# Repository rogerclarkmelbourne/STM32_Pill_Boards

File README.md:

# STM32_Pill_Boards

This repo contains a KiCad conversion of the STM32STAMP board and also two new BluePill F4 boards designed by @racemaniac and @Squonk42

My previous attemps have been deleted.

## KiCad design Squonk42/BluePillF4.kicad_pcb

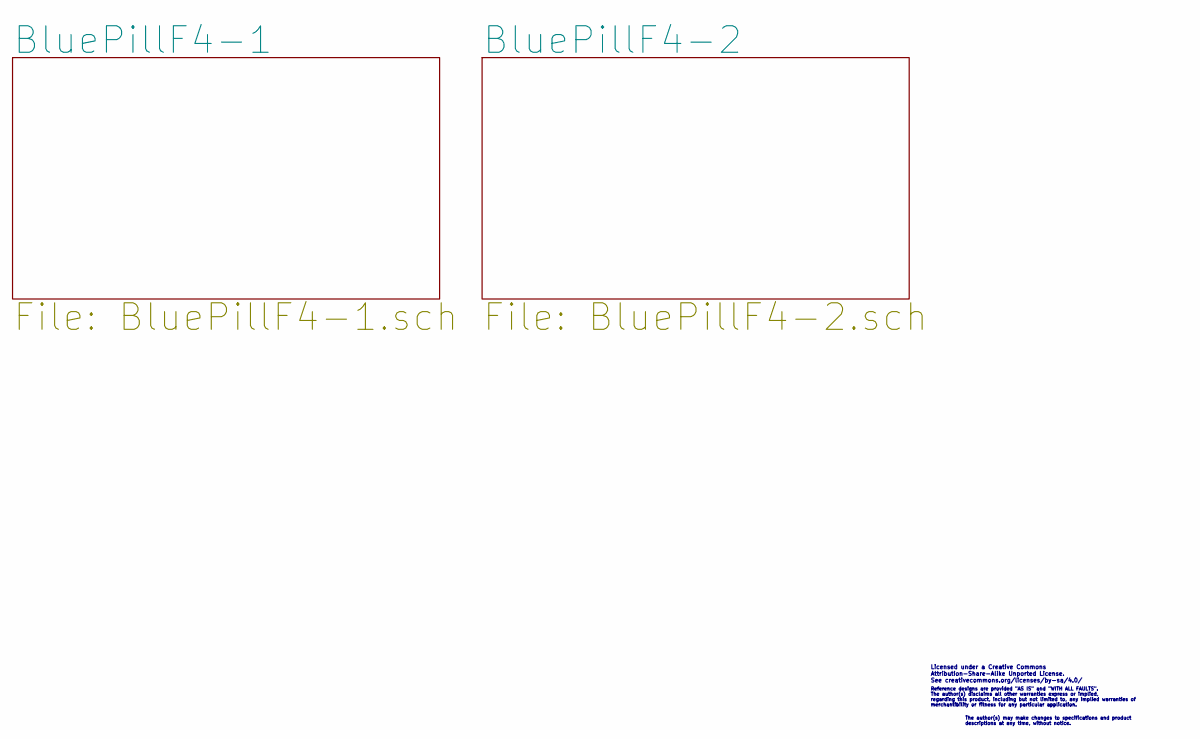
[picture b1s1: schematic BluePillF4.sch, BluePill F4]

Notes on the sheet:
Licensed under a Creative Commons Attribution-Share-Alike Unported License. See creativecommons.org/licenses/by-sa/4.0/
Reference designs are provided "AS IS" and "WITH ALL FAULTS".
The author(s) disclaims all other warranties express or implied,
regarding this product, including but not limited to, any implied warranties of
merchantibility or fitness for any particular application.
The author(s) may make changes to specifications and product
descriptions at any time, without notice.

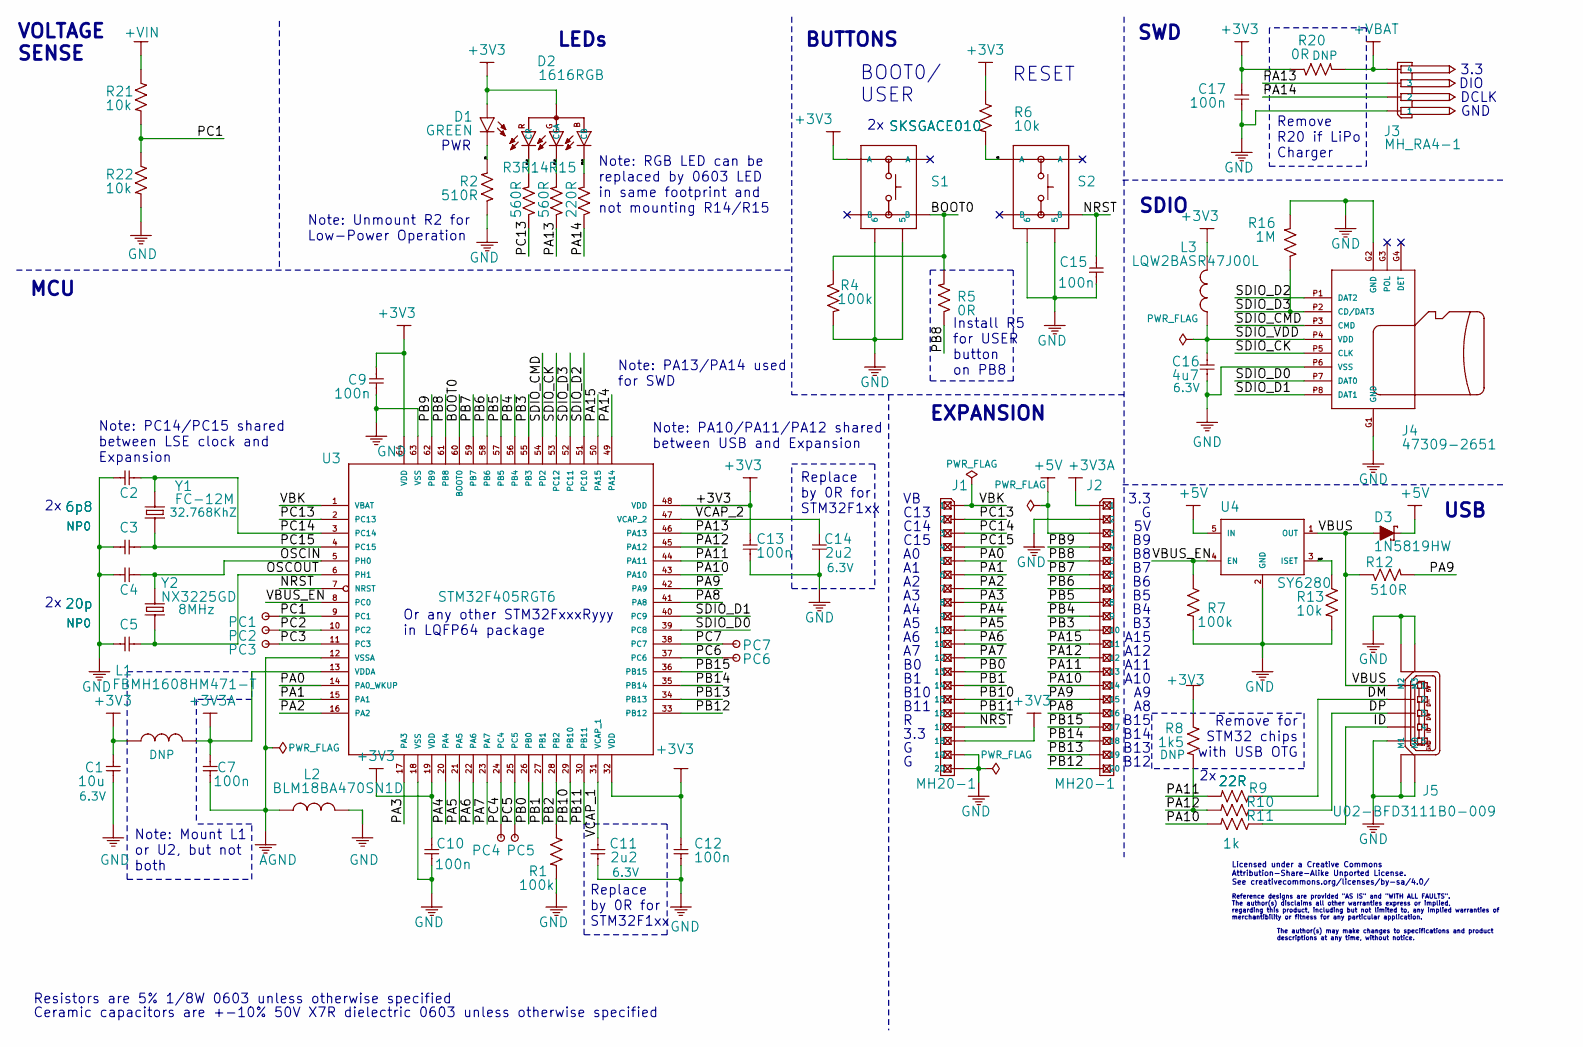
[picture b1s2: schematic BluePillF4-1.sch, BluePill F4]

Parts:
C1: 10u; C0603; PARTNO C0603_10u_X7R_10%_CER_6V3
C2, C3: 6p8; C0603; PARTNO C0603_6p8_NP0_5%_CER_50V
C4, C5: 20p; C0603; PARTNO C0603_20p_NP0_5%_CER_50V
C7, C9, C10, C12, C13, C15, C17: 100n; C0603; PARTNO C0603_100n_X7R_10%_CER_50V
C11, C14: 2u2; C0603; PARTNO C0603_2u2_X7R_10%_CER_6V3
C16: 4u7; C0603; PARTNO C0603_4u7_X7R_10%_CER_6V3
D1: GREEN; LED0603; PARTNO LED0603-GREEN
D2: 1616RGB; PARTNO LED1616-RGB
D3: 1N5819HW; SOD-123; PARTNO 1N5819HW
J1, J2: MH20-1; MH20-1-0.1; PARTNO MH20-1-0.1
J3: MH_RA4-1; MH_RA4-1-0.1; PARTNO MH_RA4-1-0.1
J4: 47309-2651; PARTNO 47309-2651
J5: U02-BFD3111B0-009; PARTNO U02-BFD3111B0-009
L1: FBMH1608HM471-T; FB0603; PARTNO FBMH1608HM471-T
L2: BLM18BA470SN1D; FB0603; PARTNO BLM18BA470SN1D
L3: LQW2BASR47J00L; FB0805; PARTNO LQW2BASR47J00L
PC1, PC2, PC3, PC4, PC5, PC6, PC7: TEST_PAD
R1, R4, R7: 100k; R0603; PARTNO R0603_100k_5%_125mW
R2, R12: 510R; R0603; PARTNO R0603_510R_5%_125mW
R3, R14: 560R; R0603; PARTNO R0603_510R_5%_125mW
R5, R20: 0R; R0603; PARTNO R0603_510R_5%_125mW
R6, R13, R21, R22: 10k; R0603; PARTNO R0603_10k_5%_125mW
R8: 1k5; R0603; PARTNO R0603_1k5_5%_125mW
R9, R10: 22R; R0603; PARTNO R0603_22R_5%_125mW
R11: 1k; R0603; PARTNO R0603_1k_5%_125mW
R15: 220R; R0603; PARTNO R0603_510R_5%_125mW
R16: 1M; R0603; PARTNO R0603_1M_5%_125mW
S1, S2: SKSGACE010; PARTNO SKSGACE010
U3: STM32F405RGT6; LQFP64; PARTNO STM32F405RGT6
U4: SY6280; SOT23-5; PARTNO SY6280AAC
Y1: FC-12M; PARTNO FC-12M 32.7680KA-A3
Y2: NX3225GD; CRYSTAL_32X25_2P; PARTNO NX3225GD-8MHZ-STD-CRA-3

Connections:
+3V3: C1.1, C9.2, C10.2, C12.1, C13.1, C17.2, D1.2 (A), D2.4 (A), J1.18, L1.1, L3.2, R6.1, R8.1, R20.1, S1.3 (A), U3.19 (VDD), U3.32 (VDD), U3.48 (VDD), U3.64 (VDD); also elsewhere on the board
+3V3A: C7.2, J2.1, L1.2, U3.13 (VDDA); also elsewhere on the board
+5V: D3.C, J2.3, U4.5 (IN); also elsewhere on the board
+VBAT: J3.4, R20.2; also elsewhere on the board
+VIN: R21.1; also elsewhere on the board
/BluePillF4-1/BOOT0: R4.1, R5.2, S1.2 (B), U3.60 (BOOT0)
/BluePillF4-1/D1: D1.1 (C), R2.2
/BluePillF4-1/D2_B: D2.3 (CB), R15.2
/BluePillF4-1/D2_G: D2.2 (CG), R14.2
/BluePillF4-1/D2_R: D2.1 (CR), R3.2
/BluePillF4-1/DM: J5.2, R9.1
/BluePillF4-1/DP: J5.3, R10.1
/BluePillF4-1/ID: J5.4, R11.1
/BluePillF4-1/ISET: R13.1, U4.3 (ISET)
/BluePillF4-1/NRST: C15.2, J1.17, S2.2 (B), U3.7 (NRST)
/BluePillF4-1/OSCIN: C4.1, U3.5 (PH0), Y2.2
/BluePillF4-1/OSCOUT: C5.1, U3.6 (PH1), Y2.1
/BluePillF4-1/PA0: J1.5, U3.14 (PA0_WKUP)
/BluePillF4-1/PA1: J1.6, U3.15 (PA1)
/BluePillF4-1/PA2: J1.7, U3.16 (PA2)
/BluePillF4-1/PA3: J1.8, U3.17 (PA3)
/BluePillF4-1/PA4: J1.9, U3.20 (PA4)
/BluePillF4-1/PA5: J1.10, U3.21 (PA5)
/BluePillF4-1/PA6: J1.11, U3.22 (PA6)
/BluePillF4-1/PA7: J1.12, U3.23 (PA7)
/BluePillF4-1/PA8: J2.16, U3.41 (PA8)
/BluePillF4-1/PA9: J2.15, R12.2, U3.42 (PA9)
/BluePillF4-1/PA10: J2.14, R11.2, U3.43 (PA10)
/BluePillF4-1/PA11: J2.13, R9.2, U3.44 (PA11)
/BluePillF4-1/PA12: J2.12, R8.2, R10.2, U3.45 (PA12)
/BluePillF4-1/PA13: J3.3, R14.1, U3.46 (PA13)
/BluePillF4-1/PA14: J3.2, R15.1, U3.49 (PA14)
/BluePillF4-1/PA15: J2.11, U3.50 (PA15)
/BluePillF4-1/PB0: J1.13, U3.26 (PB0)
/BluePillF4-1/PB1: J1.14, U3.27 (PB1)
/BluePillF4-1/PB2: R1.1, U3.28 (PB2)
/BluePillF4-1/PB3: J2.10, U3.55 (PB3)
/BluePillF4-1/PB4: J2.9, U3.56 (PB4)
/BluePillF4-1/PB5: J2.8, U3.57 (PB5)
/BluePillF4-1/PB6: J2.7, U3.58 (PB6)
/BluePillF4-1/PB7: J2.6, U3.59 (PB7)
/BluePillF4-1/PB8: J2.5, R5.1, U3.61 (PB8)
/BluePillF4-1/PB9: J2.4, U3.62 (PB9)
/BluePillF4-1/PB10: J1.15, U3.29 (PB10)
/BluePillF4-1/PB11: J1.16, U3.30 (PB11)
/BluePillF4-1/PB12: J2.20, U3.33 (PB12)
/BluePillF4-1/PB13: J2.19, U3.34 (PB13)
/BluePillF4-1/PB14: J2.18, U3.35 (PB14)
/BluePillF4-1/PB15: J2.17, U3.36 (PB15)
/BluePillF4-1/PC1: PC1.1, R21.2, R22.1, U3.9 (PC1)
/BluePillF4-1/PC2: PC2.1, U3.10 (PC2)
/BluePillF4-1/PC3: PC3.1, U3.11 (PC3)
/BluePillF4-1/PC4: PC4.1, U3.24 (PC4)
/BluePillF4-1/PC5: PC5.1, U3.25 (PC5)
/BluePillF4-1/PC6: PC6.1, U3.37 (PC6)
/BluePillF4-1/PC7: PC7.1, U3.38 (PC7)
/BluePillF4-1/PC13: J1.2, R3.1, U3.2 (PC13)
/BluePillF4-1/PC14: C2.1, J1.3, U3.3 (PC14), Y1.1
/BluePillF4-1/PC15: C3.1, J1.4, U3.4 (PC15), Y1.2
/BluePillF4-1/R6: R6.2, S2.3 (A)
/BluePillF4-1/SDIO_CK: J4.P5 (CLK), U3.53 (PC12)
/BluePillF4-1/SDIO_CMD: J4.P3 (CMD), U3.54 (PD2)
/BluePillF4-1/SDIO_D0: J4.P7 (DAT0), U3.39 (PC8)
/BluePillF4-1/SDIO_D1: J4.P8 (DAT1), U3.40 (PC9)
/BluePillF4-1/SDIO_D2: J4.P1 (DAT2), U3.51 (PC10)
/BluePillF4-1/SDIO_D3: J4.P2 (CD/DAT3), R16.1, U3.52 (PC11)
/BluePillF4-1/SDIO_VDD: C16.2, J4.P4 (VDD), L3.1
/BluePillF4-1/VBK: J1.1, U3.1 (VBAT)
/BluePillF4-1/VBUS: D3.A, J5.1, R12.1, U4.1 (OUT)
/BluePillF4-1/VBUS_EN: R7.1, U3.8 (PC0), U4.4 (EN)
/BluePillF4-1/VCAP_1: C11.2, U3.31 (VCAP_1)
/BluePillF4-1/VCAP_2: C14.2, U3.47 (VCAP_2)
AGND: C7.1, L2.1, U3.12 (VSSA); also elsewhere on the board
GND: C1.2, C2.2, C3.2, C4.2, C5.2, C9.1, C10.1, C11.1, C12.2, C13.2, C14.1, C15.1, C16.1, C17.1, J1.19, J1.20, J2.2, J3.1, J4.G1 (GND), J4.G2 (GND), J4.P6 (VSS), J5.5, J5.S$1 (M0), J5.S$2 (M1), J5.S$3 (M2), J5.S$4 (M3), L2.2, R1.2, R2.1, R4.2, R7.2, R13.2, R16.2, R22.2, S1.5, S1.6, S2.5, S2.6, U3.18 (VSS), U3.63 (VSS), U4.2 (GND); also elsewhere on the board

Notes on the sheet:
Reference designs are provided "AS IS" and "WITH ALL FAULTS".
regarding this product, including but not limited to, any implied warranties of
The author(s) may make changes to specifications and product
The author(s) disclaims all other warranties express or implied,
merchantibility or fitness for any particular application.
descriptions at any time, without notice.
Ceramic capacitors are +-10% 50V X7R dielectric 0603 unless otherwise specified
Resistors are 5% 1/8W 0603 unless otherwise specified
Remove for STM32 chips with USB OTG
Replace by 0R for STM32F1xx
RESET
BOOT0/ USER
SWD
USB
LEDs
Install R5 for USER button on PB8
PWR
SDIO
BUTTONS
EXPANSION
MCU
Note: PC14/PC15 shared between LSE clock and Expansion
Note: PA10/PA11/PA12 shared between USB and Expansion
Note: PA13/PA14 used for SWD
DIO
DCLK
3.3
GND
C13
C14
C15
B10
B11
A15
A12
A11
A10
B15
B14
B13

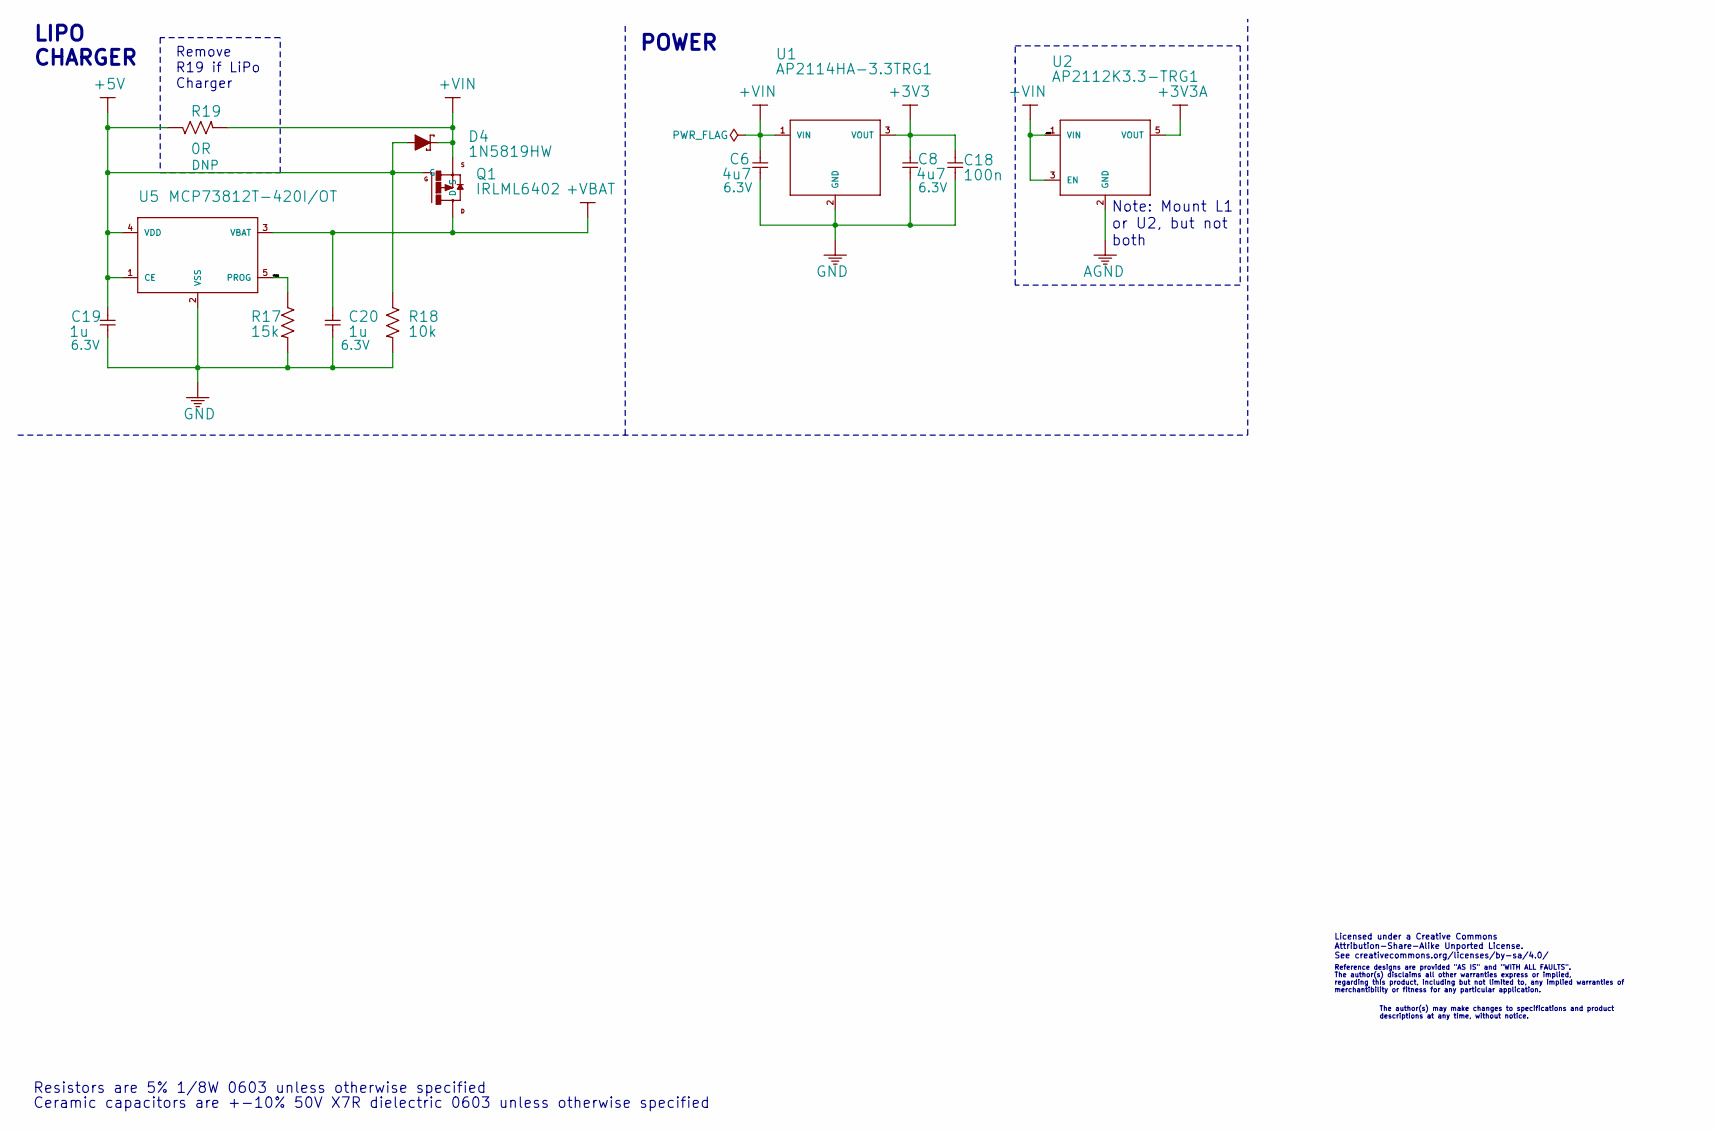
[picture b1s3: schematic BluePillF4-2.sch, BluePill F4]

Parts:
C6, C8: 4u7; C0603; PARTNO C0603_4u7_X7R_10%_CER_6V3
C18: 100n; C0603; PARTNO C0603_100n_X7R_10%_CER_50V
C19, C20: 1u; C0603; PARTNO C0603_1u_X7R_10%_CER_6V3
D4: 1N5819HW; SOD-123; PARTNO 1N5819HW
Q1: IRLML6402; SOT323
R17: 15k; R0603; PARTNO R0603_15k_5%_125mW
R18: 10k; R0603; PARTNO R0603_10k_5%_125mW
R19: 0R; R0603; PARTNO R0603_510R_5%_125mW
U1: AP2114HA-3.3TRG1; SOT223; PARTNO AP2114HA3.3-TRG1
U2: AP2112K3.3-TRG1; SOT23-5; PARTNO AP2112K3.3-TRG1
U5: MCP73812T-420I/OT; SOT23-5

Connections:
+3V3: C8.1, C18.2, U1.3 (VOUT); also elsewhere on the board
+3V3A: U2.5 (VOUT); also elsewhere on the board
+5V: C19.1, D4.A, Q1.1 (G), R18.1, R19.1, U5.1 (CE), U5.4 (VDD); also elsewhere on the board
+VBAT: C20.1, Q1.3 (D), U5.3 (VBAT); also elsewhere on the board
+VIN: C6.1, D4.C, Q1.2 (S), R19.2, U1.1 (VIN), U2.1 (VIN), U2.3 (EN); also elsewhere on the board
/BluePillF4-2/PROG: R17.1, U5.5 (PROG)
AGND: U2.2 (GND); also elsewhere on the board
GND: C6.2, C8.2, C18.1, C19.2, C20.2, R17.2, R18.2, U1.2 (GND), U1.PAD (GND), U5.2 (VSS); also elsewhere on the board

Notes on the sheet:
Licensed under a Creative Commons Attribution-Share-Alike Unported License. See creativecommons.org/licenses/by-sa/4.0/
Reference designs are provided "AS IS" and "WITH ALL FAULTS".
The author(s) disclaims all other warranties express or implied,
regarding this product, including but not limited to, any implied warranties of
merchantibility or fitness for any particular application.
The author(s) may make changes to specifications and product
descriptions at any time, without notice.
LIPO CHARGER
Resistors are 5% 1/8W 0603 unless otherwise specified
Ceramic capacitors are +-10% 50V X7R dielectric 0603 unless otherwise specified
Remove R19 if LiPo Charger
POWER
Note: Mount L1 or U2, but not both

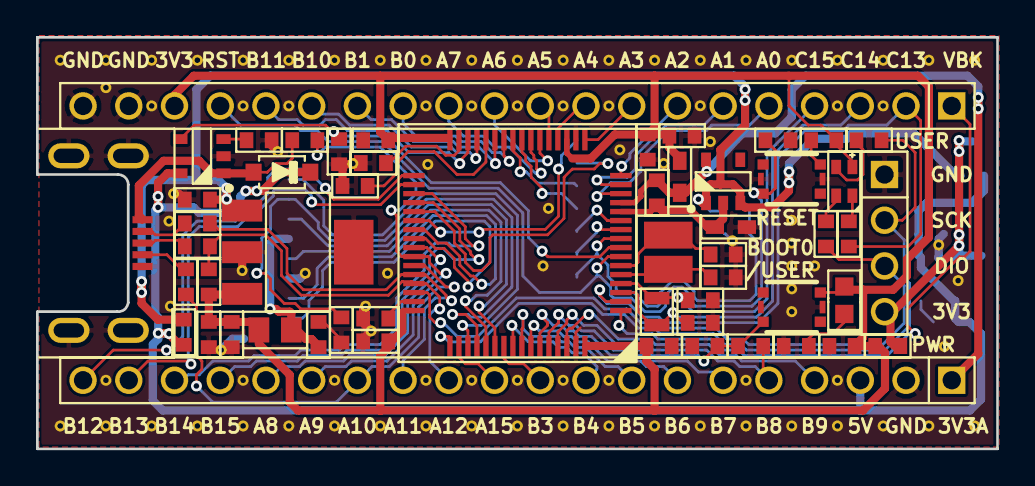
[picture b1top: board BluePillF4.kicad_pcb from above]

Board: 2 copper layers, 53.3 x 22.9 mm, 74 parts (0 on the bottom side), 75 nets.

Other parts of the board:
PC0: TEST_PAD
U$4: OPEN_HARDWARE_LOGO
U$6: RECYCLE_BIN_LOGO

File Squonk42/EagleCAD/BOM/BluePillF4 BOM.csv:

Qty-1,Part References,Value,Package,Part Num,Description,Datasheet,Digi-Key,Mouser,Aliexpress,TaoBao,XREF
1,"R5, R20(DNP)",0R,R0603,***PART# 'R0603_510R_5%_125MW' NOT FOUND***,*,*,*,*,*,*,*
0,"R19(DNP)",0R,R0603,***PART# 'R06030R_5%_125MW' NOT FOUND***,*,*,*,*,*,*,*
1,"R16",1M,R0603,***PART# 'R0603_1M_5%_125MW' NOT FOUND***,*,*,*,*,*,*,*
2,"D3, D4",1N5819HW,SOD-123,***PART# '1N5819HW' NOT FOUND***,*,*,*,*,*,*,*
1,"R11",1k,R0603,***PART# 'R0603_1K_5%_125MW' NOT FOUND***,*,*,*,*,*,*,*
0,"R8(DNP)",1k5,R0603,***PART# 'R0603_1K5_5%_125MW' NOT FOUND***,*,*,*,*,*,*,*
2,"C19, C20",1u,C0603,***PART# 'C0603_1U_X7R_10%_CER_6V3' NOT FOUND***,*,*,*,*,*,*,*
2,"C11, C14",2u2,C0603,***PART# 'C0603_2U2_X7R_10%_CER_6V3' NOT FOUND***,*,*,*,*,*,*,*
3,"C6, C8, C16",4u7,C0603,***PART# 'C0603_4U7_X7R_10%_CER_6V3' NOT FOUND***,*,*,*,*,*,*,*
2,"C2, C3",6p8,C0603,C0603_6P8_NP0_5%_CER_50V,REF9,*,*,*,*,*,*
2,"R21, R22",10k,R0603,***PART# 'R0603_10K_0.1%_125MW' NOT FOUND***,*,*,*,*,*,*,*
2,"R6, R13",10k,R0603,***PART# 'R0603_10K_5%_125MW' NOT FOUND***,*,*,*,*,*,*,*
1,"R18",10k,R0603,***PART# 'R0603_15K_5%_125MW' NOT FOUND***,*,*,*,*,*,*,*
1,"C1",10u,C0603,***PART# 'C0603_10U_X7R_10%_CER_6V3' NOT FOUND***,*,*,*,*,*,*,*
1,"R17",15k,R0603,***PART# 'R0603_15K_5%_125MW' NOT FOUND***,*,*,*,*,*,*,*
2,"C4, C5",20p,C0603,C0603_20P_NP0_5%_CER_50V,REF6,*,*,*,*,*,*
2,"R9, R10",22R,R0603,***PART# 'R0603_22R_5%_125MW' NOT FOUND***,*,*,*,*,*,*,*
3,"R1, R4, R7",100k,R0603,***PART# 'R0603_100K_5%_125MW' NOT FOUND***,*,*,*,*,*,*,*
8,"C7, C9, C10, C12, C13, C15, C17, C18",100n,C0603,C0603_100N_X7R_10%_CER_50V,REF4,*,*,*,*,*,*
5,"R15, R2, R12, R3, R14",560R,R0603,***PART# 'R0603_510R_5%_125MW' NOT FOUND***,*,*,*,*,*,*,*
1,"D2",1616RGB,1616RGB,***PART# 'LED1616-RGB' NOT FOUND***,*,*,*,*,*,*,*
1,"J4",47309-2851,47309-2851,***PART# '47309-2851' NOT FOUND***,*,*,*,*,*,*,*
0,"U2(DNP)",AP2112K3.3-TRG1,SOT23-5,***PART# 'AP2112K3.3-TRG1' NOT FOUND***,*,*,*,*,*,*,*
1,"U1",AP2114HA-3.3TRG1,SOT223,AP2114HA3.3-TRG1,REF3,*,*,*,*,*,*
1,"L2",BLM18BA470SN1D,FB0603,***PART# 'BLM18BA470SN1D' NOT FOUND***,*,*,*,*,*,*,*
1,"L1",FBMH1608HM471-T,FB0603,FBMH1608HM471-T,REF11,*,*,*,*,*,*
1,"Y1",FC-12M,FC-12M,***PART# 'FC-12M 32.7680KA-A3' NOT FOUND***,*,*,*,*,*,*,*
1,"D1",GREEN,LED0603,LED0603-GREEN,REF13,*,*,*,*,*,*
1,"Q1",IRLML6402,SOT323,***PART# 'IRLM6402' NOT FOUND***,*,*,*,*,*,*,*
1,"L3",LQW2BASR47J00L,FB0805,***PART# 'LQW2BASR47J00L' NOT FOUND***,*,*,*,*,*,*,*
1,"U5",MCP73812T-420I/OT,SOT23-5,***PART# 'MCP73812T-420I/OT' NOT FOUND***,*,*,*,*,*,*,*
2,"J1, J2",MH20-1,MH20-1-0.1,MH20-1-0.1,REF15,*,*,*,*,*,*
1,"J3",MH_RA4-1,MH_RA4-1-0.1,MH_RA4-1-0.1,REF16,*,*,*,*,*,*
1,"Y2",NX3225GD,CRYSTAL_32X25_2P,NX3225GD-8MHZ-STD-CRA-3,REF18,*,*,*,*,*,*
2,"S1, S2",SKSGACE010,SKSGACE010,SKSGACE010,REF26,*,*,*,*,*,*
1,"U3",STM32F405RGT6,LQFP64,STM32F405RGT6,REF27,*,*,*,*,*,*
1,"U4",SY6280,SOT23-5,SY6280AAC,REF28,*,*,*,*,*,*
1,"J5",U02-BFD3111B0-009,U02-BFD3111B0-009,***PART# 'U02-BFD3111B0-009' NOT FOUND***,*,*,*,*,*,*,*

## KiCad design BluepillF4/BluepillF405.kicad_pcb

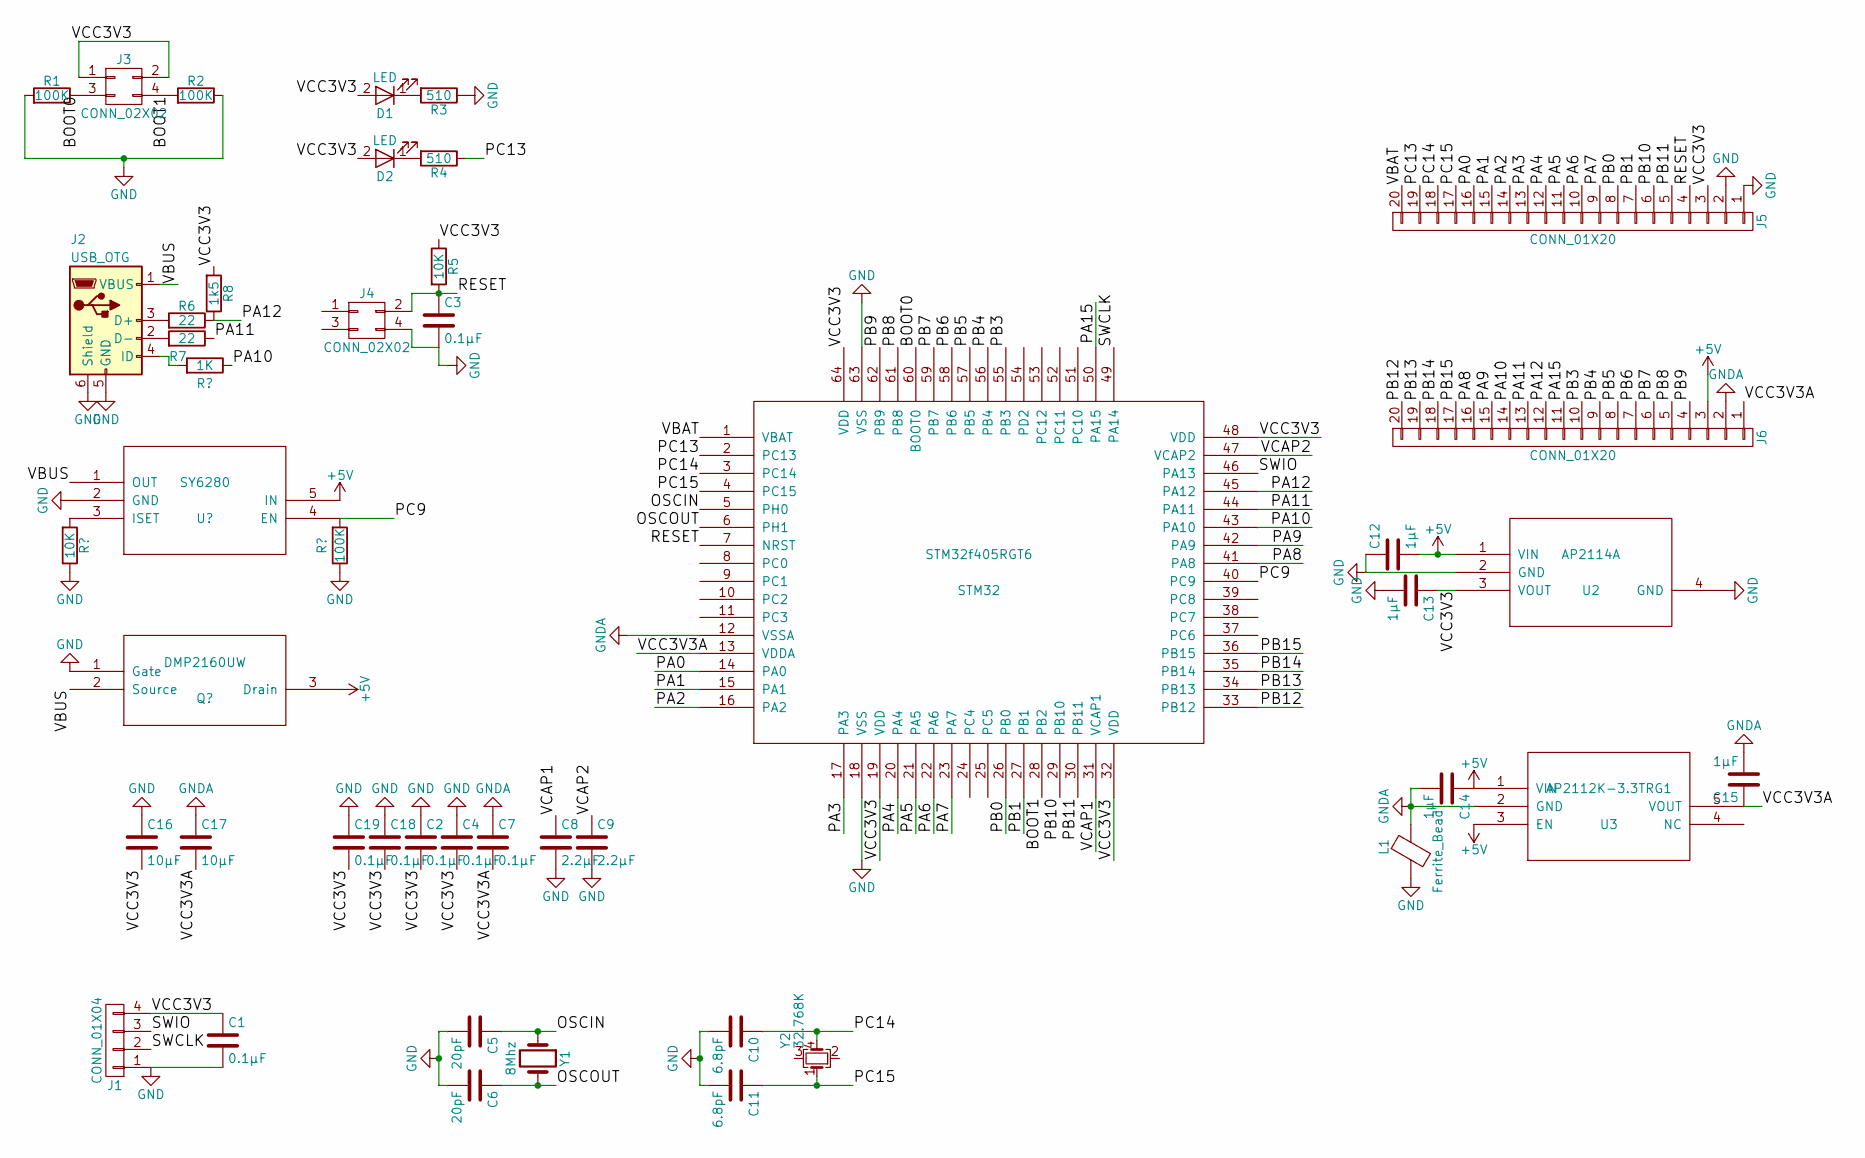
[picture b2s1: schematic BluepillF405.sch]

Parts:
C1, C2, C3, C4, C7, C18, C19: 0.1µF; C_0603
C5, C6: 20pF; C_0603
C8, C9: 2.2µF; C_0603
C10, C11: 6.8pF; C_0603
C12, C13, C14, C15: 1µF; C_0603
C16, C17: 10µF; C_0603
D1, D2: LED; LED_0805
J1: CONN_01X04; Pin_Header_Straight_1x04_Pitch2.54mm
J2: USB_OTG; USB_Micro 10118194-0001LF
J3: CONN_02X02; Pin_Header_Straight_2x02_Pitch2.54mm
J4: CONN_02X02; RS-187R05
J5, J6: CONN_01X20; Pin_Header_Straight_1x20_Pitch2.54mm
L1: Ferrite_Bead; C_0603
R1, R2: 100K; R_0603
R3, R4: 510; R_0603
R5: 10K; R_0603
R6, R7: 22; R_0603
R8: 1k5; R_0603
STM32: STM32f405RGT6; LQFP-64_10x10mm_Pitch0.5mm
U2: AP2114A; SOT-223
U3: AP2112K-3.3TRG1; SOT-23-5
Y1: 8Mhz; Crystal_HC49-U_Vertical
Y2: 32.768K; Crystal_SMD_SeikoEpson_MC306-4pin_8.0x3.2mm

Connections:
/BOOT0: J3.3, R1.1, STM32.60 (BOOT0)
/BOOT1: J3.4, R2.2, STM32.28 (PB2)
/OSCIN: C5.1, STM32.5 (PH0), Y1.1
/OSCOUT: C6.1, STM32.6 (PH1), Y1.2
/PA0: J5.16, STM32.14 (PA0)
/PA1: J5.15, STM32.15 (PA1)
/PA2: J5.14, STM32.16 (PA2)
/PA3: J5.13, STM32.17 (PA3)
/PA4: J5.12, STM32.20 (PA4)
/PA5: J5.11, STM32.21 (PA5)
/PA6: J5.10, STM32.22 (PA6)
/PA7: J5.9, STM32.23 (PA7)
/PA8: J6.16, STM32.41 (PA8)
/PA9: J6.15, STM32.42 (PA9)
/PA10: J2.4 (ID), J6.14, STM32.43 (PA10)
/PA11: J6.13, R7.1, STM32.44 (PA11)
/PA12: J6.12, R6.1, R8.1, STM32.45 (PA12)
/PA15: J6.11, STM32.50 (PA15)
/PB0: J5.8, STM32.26 (PB0)
/PB1: J5.7, STM32.27 (PB1)
/PB3: J6.10, STM32.55 (PB3)
/PB4: J6.9, STM32.56 (PB4)
/PB5: J6.8, STM32.57 (PB5)
/PB6: J6.7, STM32.58 (PB6)
/PB7: J6.6, STM32.59 (PB7)
/PB8: J6.5, STM32.61 (PB8)
/PB9: J6.4, STM32.62 (PB9)
/PB10: J5.6, STM32.29 (PB10)
/PB11: J5.5, STM32.30 (PB11)
/PB12: J6.20, STM32.33 (PB12)
/PB13: J6.19, STM32.34 (PB13)
/PB14: J6.18, STM32.35 (PB14)
/PB15: J6.17, STM32.36 (PB15)
/PC13: J5.19, R4.1, STM32.2 (PC13)
/PC14: C10.1, J5.18, STM32.3 (PC14), Y2.4
/PC15: C11.1, J5.17, STM32.4 (PC15), Y2.1
/RESET: C3.1, J4.2, J5.4, R5.2, STM32.7 (NRST)
/SWCLK: J1.2, STM32.49 (PA14)
/SWIO: J1.3, STM32.46 (PA13)
/VBAT: J5.20, STM32.1 (VBAT)
/VCAP1: C8.1, STM32.31 (VCAP1)
/VCAP2: C9.1, STM32.47 (VCAP2)
/VCC3V3: C1.1, C2.2, C4.2, C13.1, C16.2, C18.2, C19.2, D1.2 (A), D2.2 (A), J1.4, J3.1, J3.2, J5.3, R5.1, R8.2, STM32.19 (VDD), STM32.32 (VDD), STM32.48 (VDD), STM32.64 (VDD), U2.3 (VOUT)
/VCC3V3A: C7.2, C15.1, C17.2, J6.1, STM32.13 (VDDA), U3.5 (VOUT)
GND: C1.2, C2.1, C3.2, C4.1, C5.2, C6.2, C8.2, C9.2, C10.2, C11.2, C12.1, C13.2, C16.1, C18.1, C19.1, J1.1, J2.5 (GND), J2.6 (Shield), J4.4, J5.1, J5.2, L1.2, R1.2, R2.1, R3.1, STM32.18 (VSS), STM32.63 (VSS), U2.2 (GND), U2.4 (GND)
GNDA: C7.1, C14.2, C15.2, C17.1, J6.2, L1.1, STM32.12 (VSSA), U3.2 (GND)
unnamed: D1.1 (K), R3.2
unnamed: D2.1 (K), R4.2
unnamed: J2.2 (D-), R7.2
unnamed: J2.3 (D+), R6.2

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
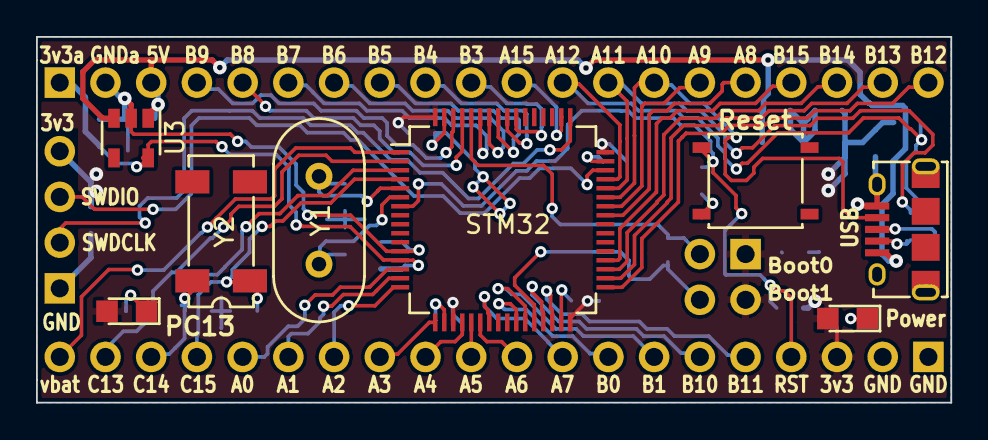
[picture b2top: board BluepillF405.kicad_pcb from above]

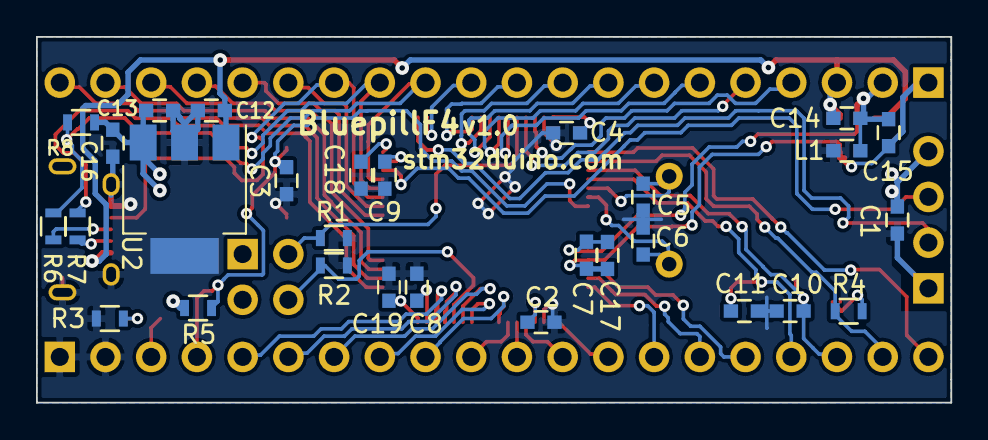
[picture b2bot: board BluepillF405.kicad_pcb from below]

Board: 2 copper layers, 50.8 x 20.3 mm, 41 parts (29 on the bottom side), 51 nets.

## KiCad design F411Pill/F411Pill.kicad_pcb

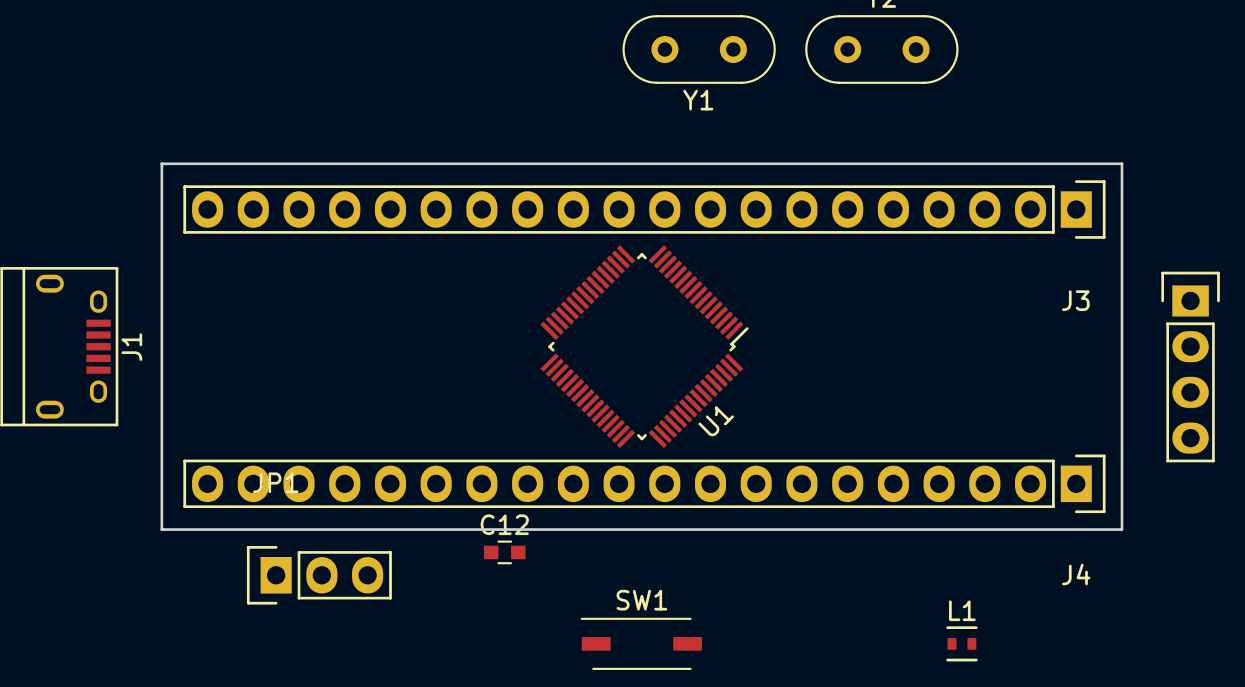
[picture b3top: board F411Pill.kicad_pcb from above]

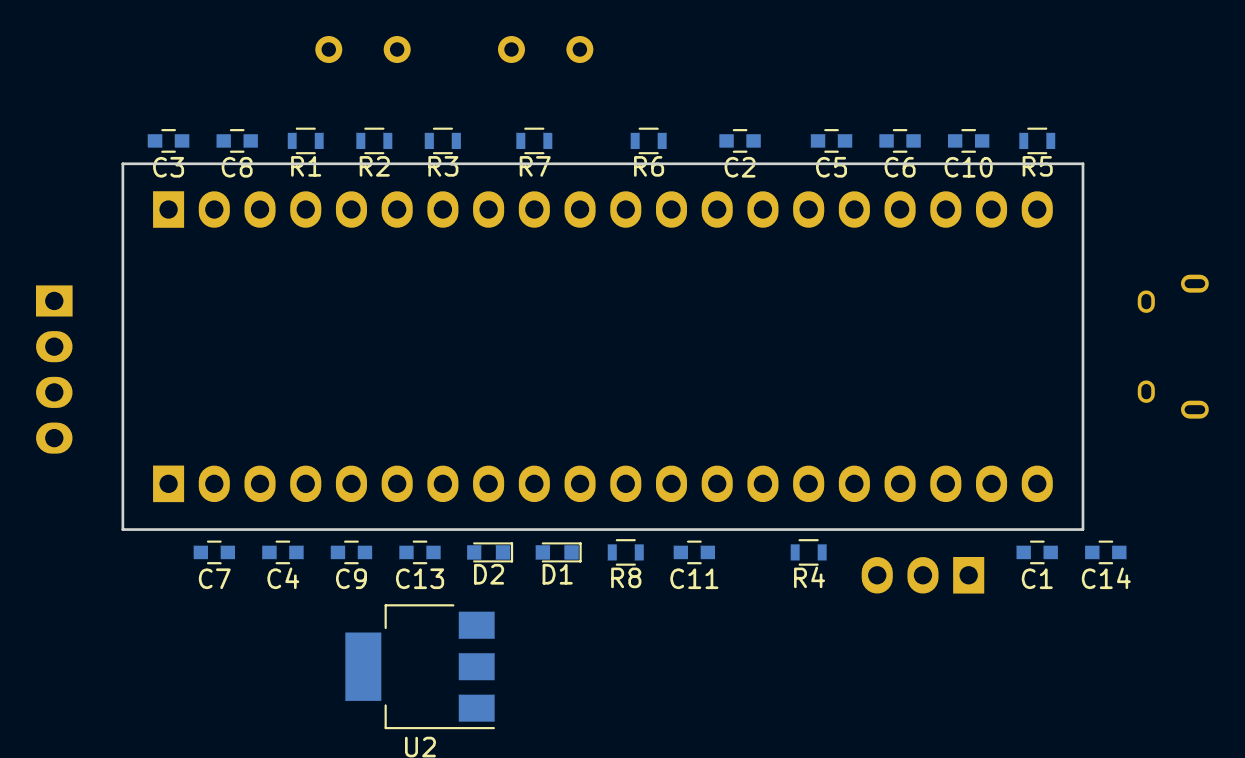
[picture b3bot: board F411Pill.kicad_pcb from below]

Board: 2 copper layers, 35 parts (24 on the bottom side), 47 nets, no tracks yet.

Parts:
C1, C2: 1u; C_0603
C3, C4, C9, C10: 20p; C_0603
C5, C8, C11, C12, C13, C14: 100n; C_0603
C6: 22n; C_0603
C7: 10u; C_0603
D1, D2: LED; LED_0603
J1: USB_A; USB_Micro-B
J2: Conn_01x04; Socket_Strip_Straight_1x04
J3, J4: Conn_01x20; Socket_Strip_Straight_1x20
JP1: Jumper_NC_Dual; Socket_Strip_Straight_1x03
L1: L_Core_Ferrite; Inductor_Taiyo-Yuden_MD-1616
R1, R2, R8: 10k; R_0603
R3, R4: 22R; R_0603
R5: 1m; R_0603
R6, R7: 510R; R_0603
SW1: SW_Push; SW_DIP_x1_W5.08mm_Slide_Copal_CHS-A
U1: STM32F411RETx; LQFP-64_7x7mm_Pitch0.4mm
U2: MCP1703A-3302_SOT223; SOT-223-3Lead_TabPin2
Y1: 8MHz; Crystal_HC52-6mm_Vertical
Y2: 32kHz; Crystal_HC52-6mm_Vertical

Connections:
+3V3: C7.1, C8.1, C11.1, C12.1, C13.1, C14.1, D2.2, J2.1, J3.18, J4.1, R6.2, U1.19, U1.32, U1.48, U1.64, U2.3
+5V: C2.1, C5.1, C6.1, J1.1, J4.3, U2.1
/BOOT0: R2.1, U1.60
/NRST: C1.1, J3.17, R1.2, SW1.2, U1.7
/OSCIN: C3.1, R5.2, U1.5, Y1.1
/OSCOUT: C4.1, R5.1, U1.6, Y1.2
/PA0: J3.5, U1.14
/PA1: J3.6, U1.15
/PA2: J3.7, U1.16
/PA3: J3.8, U1.17
/PA4: J3.9, U1.20
/PA5: J3.10, U1.21
/PA6: J3.11, U1.22
/PA7: J3.12, U1.23
/PA8: J4.16, U1.41
/PA9: J4.15, U1.42
/PA10: J4.14, U1.43
/PA11: J4.13, R3.1, U1.44
/PA12: J4.12, R4.1, U1.45
/PA15: J4.11, U1.50
/PB0: J3.13, U1.26
/PB1: J3.14, U1.27
/PB2: R8.2, U1.28
/PB3: J4.10, U1.55
/PB4: J4.9, U1.56
/PB5: J4.8, U1.57
/PB6: J4.7, U1.58
/PB7: J4.6, U1.59
/PB8: J4.5, U1.61
/PB9: J4.4, U1.62
/PB10: J3.15, U1.29
/PB12: J4.20, U1.33
/PB13: J4.19, U1.34
/PB14: J4.18, U1.35
/PB15: J4.17, U1.36
/PC13: C10.1, J3.2, R7.2, U1.2, Y2.2
/PC14: C9.1, J3.3, U1.3, Y2.1
/PC15: J3.4, U1.4
/VBAT: J3.1, U1.1
GND: C1.2, C2.2, C3.2, C4.2, C5.2, C6.2, C7.2, C8.2, C9.2, C10.2, C11.2, C12.2, C13.2, C14.2, D1.1, J1.4, J1.5, J2.4, J3.19, J3.20, J4.2, JP1.3, L1.1, R8.1, SW1.1, U1.18, U1.31, U1.47, U1.63, U2.2
GNDA: L1.2, U1.12
unnamed: D1.2, R6.1
unnamed: D2.1, R7.1
unnamed: J1.2, R4.2
unnamed: J1.3, R3.2
unnamed: JP1.1, R1.1
unnamed: JP1.2, R2.2

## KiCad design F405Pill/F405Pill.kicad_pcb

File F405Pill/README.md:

# F405Pill
STM32F405RG development board based on the STM32STAMP board

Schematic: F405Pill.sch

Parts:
C1, C9, C10: 4u7; EIA3216-KIT
C2, C3, C4, C5, C6: 100n; 0603-CAP
C7, C8: 2u2; 0603-CAP
C11: 470p; 0603-CAP
C12, C13: 22p; 0603-CAP
IC1: VREG-3V3; SOT23-5
JMP-HOLDER57: 1X02_2MM_TH
JMP-UID57: SJ_2S
JMP-USB57: 1X02_2MM_TH
JP2: 5V; 1X1-HEADER-HOLE
JP3, JP5, JP6, JP7: GND; 1X1-HEADER-HOLE
JP4: 3V3; 1X1-HEADER-HOLE
JP8: PB8; 1X1-HEADER-HOLE
JP9: PA10; 1X1-HEADER-HOLE
JP10: PA8; 1X1-HEADER-HOLE
JP11: PA13; 1X1-HEADER-HOLE
JP12: PC9; 1X1-HEADER-HOLE
JP13: PC15; 1X1-HEADER-HOLE
JP14: PC14; 1X1-HEADER-HOLE
JP15: PC13; 1X1-HEADER-HOLE
JP16: PC12; 1X1-HEADER-HOLE
JP17: PC11; 1X1-HEADER-HOLE
JP18: PC10; 1X1-HEADER-HOLE
JP19: PC8; 1X1-HEADER-HOLE
JP20: PC7; 1X1-HEADER-HOLE
JP21: PC6; 1X1-HEADER-HOLE
JP22: PC5; 1X1-HEADER-HOLE
JP23: PC4; 1X1-HEADER-HOLE
JP24: PC3; 1X1-HEADER-HOLE
JP25: PC2; 1X1-HEADER-HOLE
JP26: PC1; 1X1-HEADER-HOLE
JP27: PC0; 1X1-HEADER-HOLE
JP28: PD2; 1X1-HEADER-HOLE
JP29: PA0; 1X1-HEADER-HOLE
JP30: PA1; 1X1-HEADER-HOLE
JP31: PA2; 1X1-HEADER-HOLE
JP32: PA3; 1X1-HEADER-HOLE
JP33: PA4; 1X1-HEADER-HOLE
JP34: PA5; 1X1-HEADER-HOLE
JP35: PA6; 1X1-HEADER-HOLE
JP36: PA7; 1X1-HEADER-HOLE
JP37: PA14; 1X1-HEADER-HOLE
JP38: PA15; 1X1-HEADER-HOLE
JP39: PB0; 1X1-HEADER-HOLE
JP40: PB1; 1X1-HEADER-HOLE
JP41: PB3; 1X1-HEADER-HOLE
JP42: PB4; 1X1-HEADER-HOLE
JP43: PB5; 1X1-HEADER-HOLE
JP44: PB6; 1X1-HEADER-HOLE
JP45: PB7; 1X1-HEADER-HOLE
JP46: PB9; 1X1-HEADER-HOLE
JP47: PB10; 1X1-HEADER-HOLE
JP48: PB11; 1X1-HEADER-HOLE
JP49: PB12; 1X1-HEADER-HOLE
JP50: PB13; 1X1-HEADER-HOLE
JP51: PB14; 1X1-HEADER-HOLE
JP52: PB15; 1X1-HEADER-HOLE
JP53: VBAT; 1X1-HEADER-HOLE
JP54: !RST; 1X1-HEADER-HOLE
JP55: BOOT0; 1X1-HEADER-HOLE
JP56: USB-ID; 1X1-HEADER-HOLE
LED1: LED-0603
R1, R2: 22R; 0603-RES
R3: 470R; 0603-RES
R4, R5: 10K; 0603-RES
R6: 1.5k; 0603-RES
SW1: !RST; SWITCH-TACT-B3U-1100P-B
SW2: BOOT; SWITCH-TACT-B3U-1100P-B
U1: STM32F405RGT; LQFP64
USB57: USB-MICROB-SMD
VP_0, VP_1, VP_2, VP_3, VP_4, VP_5, VP_6, VP_7, VP_8, VP_9, VP_10, VP_11, VP_12, VP_13, VP_14, VP_15, VP_16, VP_17, VP_18, VP_19, VP_20, VP_21, VP_22, VP_23, VP_24, VP_25, VP_26, VP_27: VPDEV0; VPAC0
Y1: 8MHz; CRYSTAL-SMD-5X3

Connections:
3.3V: C2.1, C3.1, C4.1, C5.1, C6.1, C10.A (+), IC1.5 (OUT), JP4.1, LED1.A, R4.2, R6.1, SW2.1, U1.13 (VDDA), U1.19 (VDD1), U1.32 (VDD2), U1.48 (VDD3), U1.64 (VDD4)
5V: C9.A (+), IC1.1 (IN), IC1.3 (EN), JMP-USB57.2, JP2.1
/N$1: R1.2, R6.2, U1.45 (USB_DP(PA12))
/N$2: R2.2, U1.44 (USB_DM(PA11))
/N$3: C1.A (+), JMP-USB57.1, U1.42 (VBUS(PA9)), USB57.VBUS
/N$4: JP12.1, U1.40 (PC9)
/N$5: R1.1, USB57.D+
/N$6: R2.1, USB57.D-
/N$7: JP8.1, U1.61 (PB8)
/N$8: C11.2, IC1.4 (BP)
/N$10: JP10.1, U1.41 (PA8)
/N$11: JP11.1, U1.46 (PA13)
/N$12: C13.1, U1.6 (OSC_OUT(PH1)), Y1.1
/N$13: C7.1, U1.31 (VCAP_1)
/N$14: C8.1, U1.47 (VCAP_2)
/N$15: C12.1, U1.5 (OSC_IN(PH0)), Y1.3 (2)
/N$16: JP55.1, R5.1, SW2.2, U1.60 (BOOT0)
/N$17: JP54.1, R4.1, SW1.1, U1.7 (NRST)
/N$18: LED1.C, R3.2
/N$20: JMP-UID57.2, JP56.1, USB57.ID
/N$22: JMP-UID57.1, JP9.1, U1.43 (PA10)
/N$23: JP13.1, U1.4 (PC15)
/N$24: JP14.1, U1.3 (PC14)
/N$25: JP15.1, U1.2 (PC13)
/N$26: JP16.1, U1.53 (PC12)
/N$27: JP17.1, U1.52 (PC11)
/N$28: JP18.1, U1.51 (PC10)
/N$29: JP19.1, U1.39 (PC8)
/N$30: JP20.1, U1.38 (PC7)
/N$31: JP21.1, U1.37 (PC6)
/N$32: JP22.1, U1.25 (PC5)
/N$33: JP23.1, U1.24 (PC4)
/N$34: JP24.1, U1.11 (PC3)
/N$35: JP25.1, U1.10 (PC2)
/N$36: JP26.1, U1.9 (PC1)
/N$37: JP27.1, U1.8 (PC0)
/N$38: JP28.1, U1.54 (PD2)
/N$39: JP29.1, U1.14 (PA0)
/N$40: JP30.1, U1.15 (PA1)
/N$41: JP31.1, U1.16 (PA2)
/N$42: JP32.1, U1.17 (PA3)
/N$43: JP33.1, U1.20 (PA4)
/N$44: JP34.1, U1.21 (PA5)
/N$45: JP35.1, U1.22 (PA6)
/N$46: JP36.1, U1.23 (PA7)
/N$47: JP37.1, U1.49 (PA14)
/N$48: JP38.1, U1.50 (PA15)
/N$49: JP39.1, U1.26 (PB0)
/N$50: JP40.1, U1.27 (PB1)
/N$51: JP41.1, U1.55 (PB3)
/N$52: JP42.1, U1.56 (PB4)
/N$53: JP43.1, U1.57 (PB5)
/N$54: JP44.1, U1.58 (PB6)
/N$55: JP45.1, U1.59 (PB7)
/N$56: JP46.1, U1.62 (PB9)
/N$57: JP47.1, U1.29 (PB10)
/N$58: JP48.1, U1.30 (PB11)
/N$59: JP49.1, U1.33 (PB12)
/N$60: JP50.1, U1.34 (PB13)
/N$61: JP51.1, U1.35 (PB14)
/N$62: JP52.1, U1.36 (PB15)
/N$63: JP53.1, U1.1 (VBAT)
GND: C1.C (-), C2.2, C3.2, C4.2, C5.2, C6.2, C7.2, C8.2, C9.C (-), C10.C (-), C11.1, C12.2, C13.2, IC1.2 (GND), JP3.1, JP5.1, JP6.1, JP7.1, R3.1, R5.2, SW1.2, SW1.BOSS, SW2.BOSS, U1.12 (VSSA), U1.18 (VSS1), U1.28 (BOOT1(PB2)), U1.63 (VSS2), USB57.GND, USB57.MT1, USB57.MT2, USB57.MT3, USB57.MT4, VP_0.VP, VP_1.VP, VP_2.VP, VP_3.VP, VP_4.VP, VP_5.VP, VP_6.VP, VP_7.VP, VP_8.VP, VP_9.VP, VP_10.VP, VP_11.VP, VP_12.VP, VP_13.VP, VP_14.VP, VP_15.VP, VP_16.VP, VP_17.VP, VP_18.VP, VP_19.VP, VP_20.VP, VP_21.VP, VP_22.VP, VP_23.VP, VP_24.VP, VP_25.VP, VP_26.VP, VP_27.VP

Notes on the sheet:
F405Pill based on STM32F4Stamp Frank Zhao 20131027

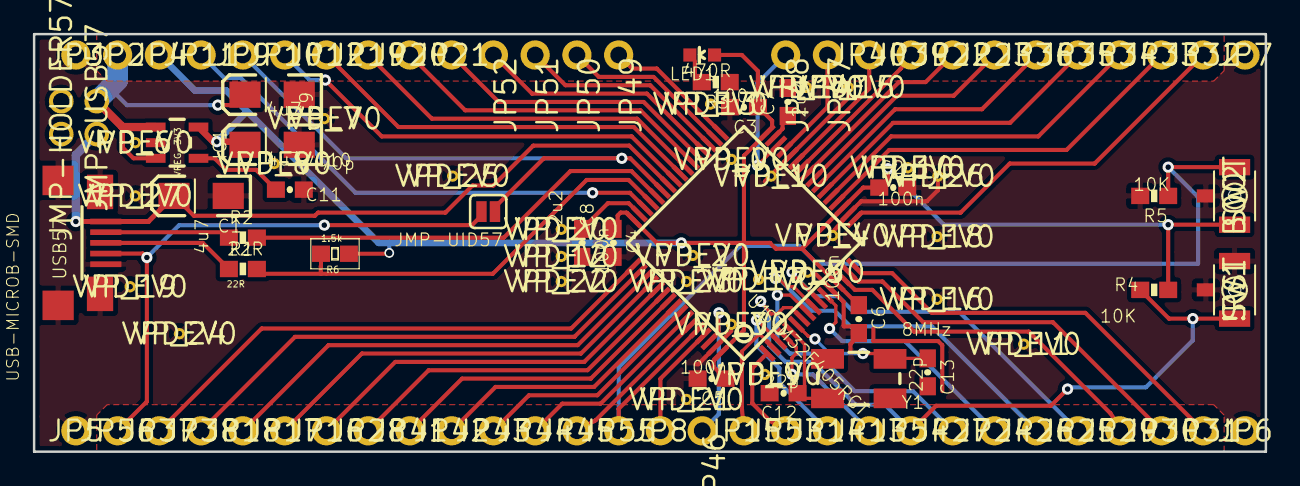
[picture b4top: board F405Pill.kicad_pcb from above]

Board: 2 copper layers, 74.9 x 25.4 mm, 112 parts (0 on the bottom side), 63 nets.

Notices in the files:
Squonk42/BluePillF4-1.sch:
© 2017-2018 www.stm32duino.com, All rights reserved.
Squonk42/BluePillF4.kicad_pcb:
© 2017-2018, All rights reserved.
CC-BY-SA
Squonk42/EagleCAD/BluePillF4.sch:
© 2017-2018,
parts and their libraries:
BluePillF4: See creativecommons.org/licenses/by-sa/4.0/ for details.
BluePillF4: See creativecommons.org/licenses/by-sa/3.0/ for details.
